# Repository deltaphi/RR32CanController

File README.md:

# RR32CanSwitchboard
Sketch for a Switchboard talking the Maerklin CAN protocol based on the ESP32 NodeMCU-Board.

Special Note: This sketch uses an experimental release of Arduino-ESP32. If you get errors from the compiler or the linker, make sure to (1) clean out as much of PlatformIO as you can without actually uninstalling it and (2) get a fresh checkout of this project.

## CI Status

* Linux Unittest Build

* Embedded Build

* Windows Unittest Build

## Software

This project is built using PlatformIO. It makes use of some features that may
not be easily portable to other Arduino-supported MCUs.

### Library Notes

This project makes use of several libraries. Versioned links to those libraries
are available as git submodules. Note that for seom libraries, using forks from
the same source as this project may be required.

Note that the CAN driver from the lib directory *must not* be present when you
want to compile using the ESP32-IDF driver. Otherwise, the Controller will just
attempt to sit there without sending queued messages or receiving any messages
transmitted on the bus.

### WiFi

This sketch only supports runtime-selection of CAN connection vs. WiFi
connection. The WiFi connection information (SSID, Password, IP of CAN-Gateway)
must be hardcoded.

To support hardcoding, a template file "_wificonfig.h" is provided. Copy the
template to "wificonfig.h" and adjust the configuration information to your
needs.

### Menuing

#### General concept

General: Shift + Direction Change enters the menu (cycles through menus) or leaves the menu without applying any changes.

Menu Levels:

* Level 0/Default: Loco Control
* Level 1: Loco List
* Level 2: Settings Menu

#### Menuing for Accessories

Menuing is required to map turnout input buttons to turnouts or action lists.

TODO: Design.

#### Menuing for Engine Control

Menuing is required for selecting an engine to control. This involves the following usecases:

* Select locally known engine
    * Show list of locally known Engines
    * Select engine
    * Selected Engine is now the active engine

* Select locally unknown engine
    * Verify that at least one local slot for an engine is open
    * If not:
        * Promt the user to remove an engine from the local database to be able to download a new one.
        * Show list of locally known Engines
        * Select an engine.
        * Selected Engine is marked for replacement
    * If yes:
        * Empty engine slot with lowest index is marked for replacement
    * Download list of Engines & total number of known engines from the master controller.
    * Either: Select engine from the master list
        * Details of Selected engine are downloaded.
    * Either: Scroll up/down beyond the currently known set of engine names.
        * If the engine name is unknown, download list of engines from the master controller.
    * Once the download is complete, the selected engine is now the active engine

#### Encoder Acceleration for Engine Control

Formula for acceleration curve: y = m*x + c. x is the time since the last rotation in the same direction,
y is the number of actual increments to apply.

The acceleration is linear. It should be set up so that there is a cutoff at 500ms (no acceleration when
increments are more than half a second apart) and that an "immediate" half rotation (e.g., within 50ms)
hits the opposite end of engine velocity.

Thus, boundary conditions for an encoder with 24 increments per rotaton are:
1 Tick = m*500ms + c
kMaxEngineVelocity Ticks / 12 increments = m * (50ms / 12 increments) + c

Formulas for calculating m and c:

m = (y1 - y2)/(x1 - x2) = (1 - (kMaxEngineVelocity/12))/(500 - (50/12)) = -0.16

c = y1 - m*x1 = 84.03

#### Settings Menu

Menu Entries:

* Turnout mapping
* Action list mapping
* Default connection settings
* WiFi settings

##### Turnout Mapping

When in the Turnout mapping menu:

* Press a button (red or green) for a turnout
* Display shows number of button and whether red or green was pressed (line 1)
* Display shows human-readable number of currently mapped turnout
* Use encoder to adjust the number of the turnout
* pressing the encoder stores the turnout mapping (visual feedback possible?)
* pressing another turnout button switches to settings for that button
* pressing shift + encoder leaves the menu.

Possible extension: Use the function buttons to increase/decrease in steps of 10

### Unit Testing

This project includes a CMake project.
The CMake project is purely used to run unit tests for some parts of the code on your development machine.
You do not need to deal with unit tests (or the CMake project) unless you want to actively develop the software.
To use the CMake project, create an out-of-tree build directoy (in-tree build will confuse the Automagic of PlatformIO).
Unit testing should be possible using any C++14 capable compiler on any Desktop Operating System.
It has been tested successefully using MSVC 2017 Community Edition.

## Hardware

### PCB

There is a KiCAD PCB design included for turning this project into a handheld device.
The PCB is designed for the [Strapubox 2090 case](https://www.reichelt.de/kunststoffgehaeuse-129-x-40-x-26-mm-sp-2090-sw-p33828.html?&trstct=pos_0).

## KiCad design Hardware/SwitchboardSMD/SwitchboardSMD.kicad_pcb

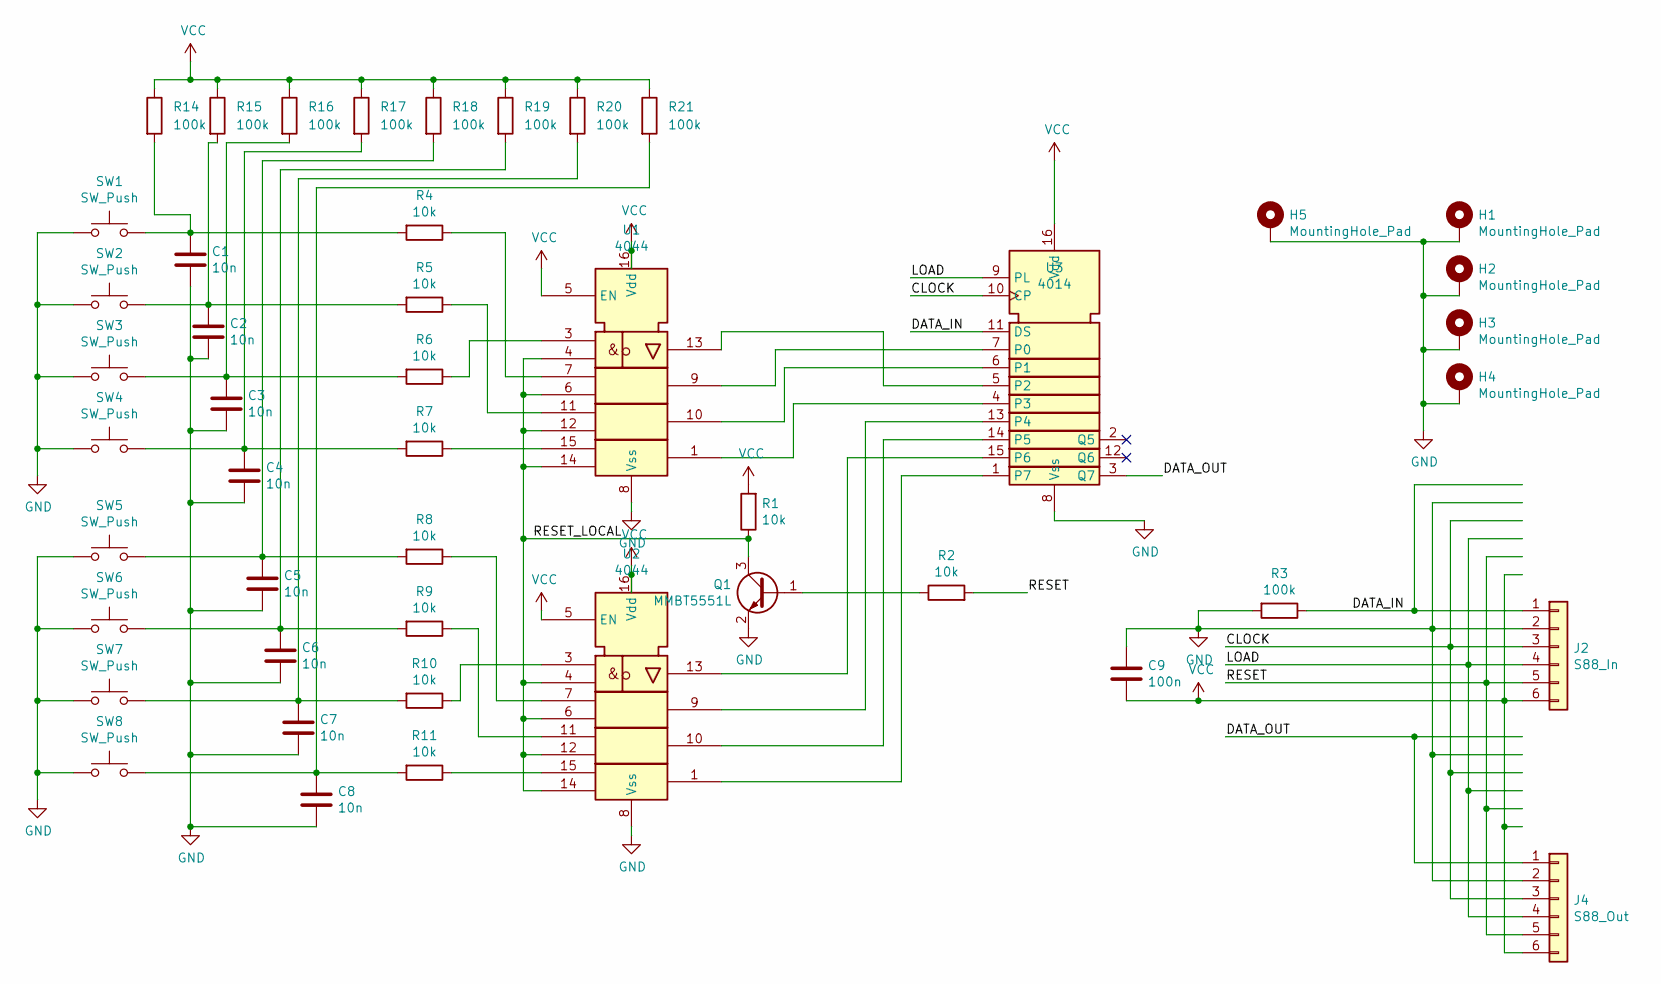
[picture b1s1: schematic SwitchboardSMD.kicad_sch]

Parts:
C1, C2, C3, C4, C5, C6, C7, C8: 10n; C_1206_3216Metric
C9: 100n; C_1206_3216Metric
H1, H2, H3, H4: MountingHole_Pad; MountingHole_2.2mm_M2
H5: MountingHole_Pad; MountingHole_3.2mm_M3_Pad_Via
J2: S88_In; PinSocket_1x06_P2.54mm_Horizontal
J4: S88_Out; PinHeader_1x06_P2.54mm_Horizontal
Q1: MMBT5551L; SOT-23
R1, R2, R4, R5, R6, R7, R8, R9, R10, R11: 10k; R_1206_3216Metric_Pad1.30x1.75mm_HandSolder
R3, R14, R15, R16, R17, R18, R19, R20, R21: 100k; R_1206_3216Metric_Pad1.30x1.75mm_HandSolder
SW1, SW2, SW3, SW4, SW5, SW6, SW7, SW8: SW_Push; SW_PUSH_6mm
U1, U2: 4044; TSSOP-16_4.4x5mm_P0.65mm
U3: 4014; TSSOP-16_4.4x5mm_P0.65mm

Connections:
/CLOCK: J2.3, J4.3, U3.10 (CP)
/DATA_IN: J2.1, R3.1, U3.11 (DS)
/DATA_OUT: J4.1, U3.3 (Q7)
/LOAD: J2.4, J4.4, U3.9 (PL)
/RESET: J2.5, J4.5, R2.2
/RESET_LOCAL: Q1.3 (C), R1.1, U1.4, U1.6, U1.12, U1.14, U2.4, U2.6, U2.12, U2.14
GND: C1.2, C2.2, C3.2, C4.2, C5.2, C6.2, C7.2, C8.2, C9.1, H1.1, H2.1, H3.1, H4.1, H5.1, J2.2, J4.2, Q1.2 (E), R3.2, SW1.1, SW2.1, SW3.1, SW4.1, SW5.1, SW6.1, SW7.1, SW8.1, U1.8 (Vss), U2.8 (Vss), U3.8 (Vss)
unnamed: C1.1, R4.2, R14.2, SW1.2
unnamed: C2.1, R5.2, R15.2, SW2.2
unnamed: C3.1, R6.2, R16.2, SW3.2
unnamed: C4.1, R7.2, R17.2, SW4.2
unnamed: C5.1, R8.2, R18.2, SW5.2
unnamed: C6.1, R9.2, R19.2, SW6.2
unnamed: C7.1, R10.2, R20.2, SW7.2
unnamed: C8.1, R11.2, R21.2, SW8.2
unnamed: Q1.1 (B), R2.1
unnamed: R4.1, U1.7
unnamed: R5.1, U1.11
unnamed: R6.1, U1.3
unnamed: R7.1, U1.15
unnamed: R8.1, U2.7
unnamed: R9.1, U2.11
unnamed: R10.1, U2.3
unnamed: R11.1, U2.15
unnamed: U1.9, U3.7 (P0)
unnamed: U1.10, U3.6 (P1)
unnamed: U1.13, U3.5 (P2)
unnamed: U1.1, U3.4 (P3)
unnamed: U2.9, U3.13 (P4)
unnamed: U2.10, U3.14 (P5)
unnamed: U2.13, U3.15 (P6)
unnamed: U2.1, U3.1 (P7)
VCC: C9.2, J2.6, J4.6, R1.2, R14.1, R15.1, R16.1, R17.1, R18.1, R19.1, R20.1, R21.1, U1.5 (EN), U1.16 (Vdd), U2.5 (EN), U2.16 (Vdd), U3.16 (Vdd)

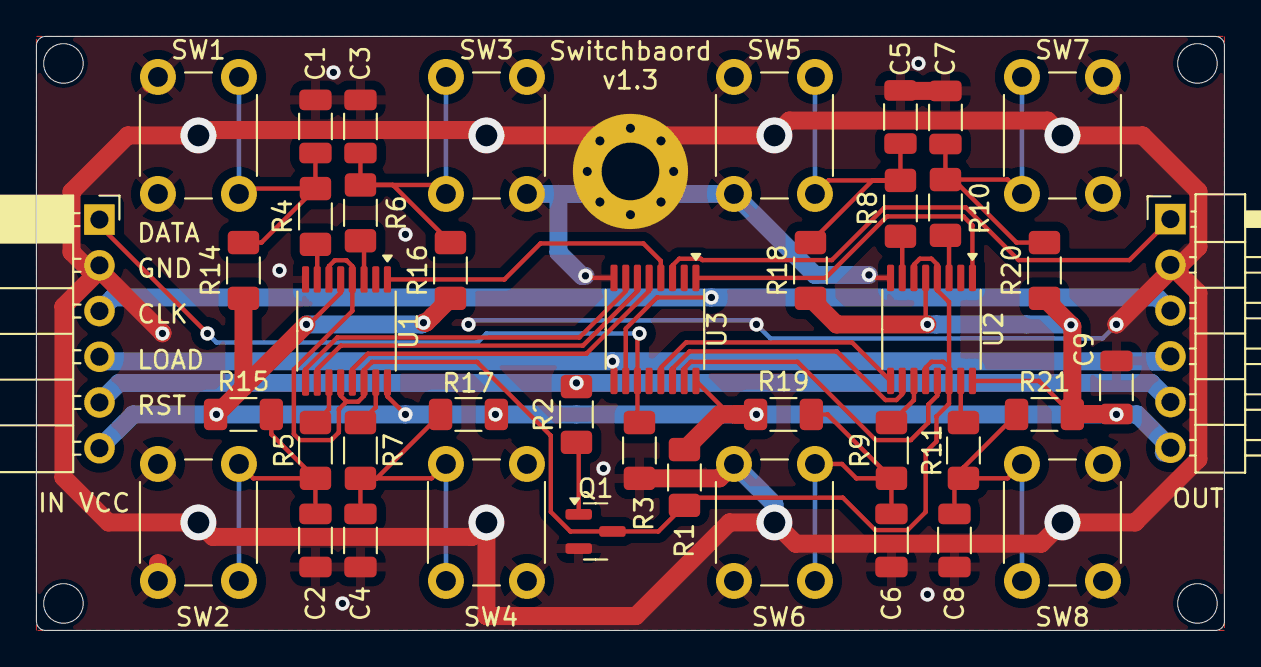
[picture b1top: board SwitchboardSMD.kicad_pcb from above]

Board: 2 copper layers, 66.0 x 33.0 mm, 47 parts (0 on the bottom side), 33 nets.

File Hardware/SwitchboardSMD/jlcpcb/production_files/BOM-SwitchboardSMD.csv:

Comment,Designator,Footprint,LCSC,Quantity
100k,"R14,R15,R16,R17,R18,R19,R20,R21,R3",R_1206_3216Metric_Pad1.30x1.75mm_HandSolder,C17900,9
10k,"R1,R10,R11,R2,R4,R5,R6,R7,R8,R9",R_1206_3216Metric_Pad1.30x1.75mm_HandSolder,C17902,10
10n,"C1,C2,C3,C4,C5,C6,C7,C8",C_1206_3216Metric,C1846,8
100n,C9,C_1206_3216Metric,C24497,1
4014,U3,TSSOP-16_4.4x5mm_P0.65mm,C2877059,1
MMBT5551L,Q1,SOT-23,C41095,1
4044,"U1,U2",TSSOP-16_4.4x5mm_P0.65mm,C74801,2
SW_Push,SW1,SW_PUSH_6mm,,1
MountingHole_Pad,H1,MountingHole_2.2mm_M2,,1
MountingHole_Pad,H2,MountingHole_2.2mm_M2,,1
MountingHole_Pad,H3,MountingHole_2.2mm_M2,,1
MountingHole_Pad,H4,MountingHole_2.2mm_M2,,1
SW_Push,SW2,SW_PUSH_6mm,,1
SW_Push,SW3,SW_PUSH_6mm,,1
SW_Push,SW5,SW_PUSH_6mm,,1
SW_Push,SW6,SW_PUSH_6mm,,1
SW_Push,SW7,SW_PUSH_6mm,,1
SW_Push,SW8,SW_PUSH_6mm,,1
SW_Push,SW4,SW_PUSH_6mm,,1
S88_In,J2,PinSocket_1x06_P2.54mm_Horizontal,,1
S88_Out,J4,PinHeader_1x06_P2.54mm_Horizontal,,1
MountingHole_Pad,H5,MountingHole_3.2mm_M3_Pad_Via,,1

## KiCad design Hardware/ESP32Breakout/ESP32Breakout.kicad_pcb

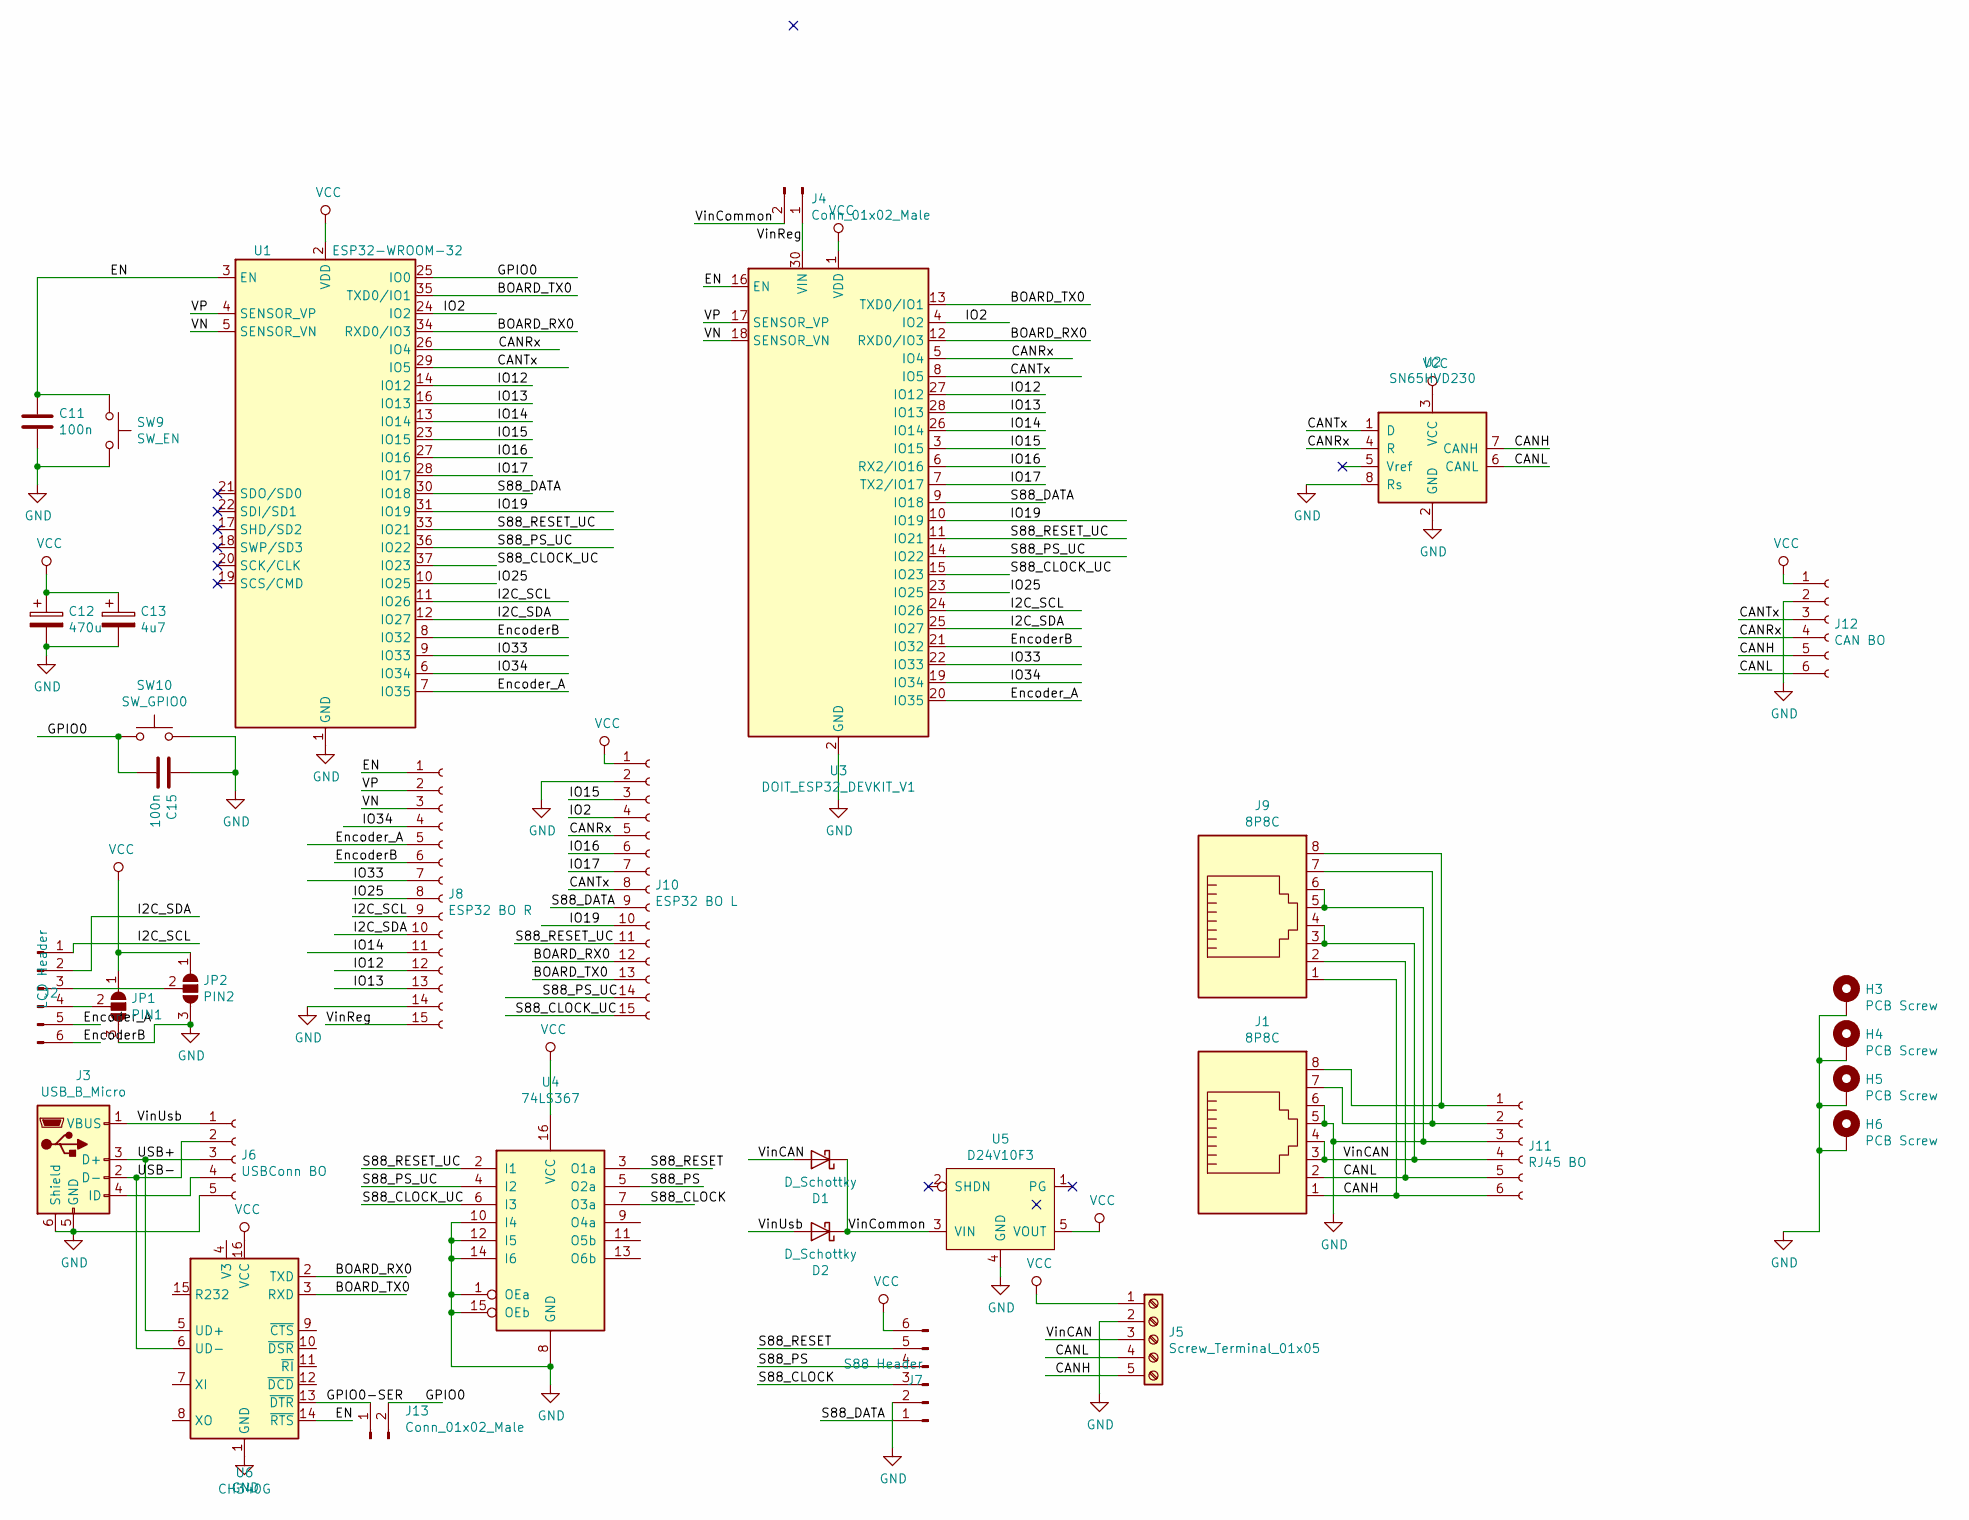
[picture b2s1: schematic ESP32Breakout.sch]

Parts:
C11, C15: 100n; C_Disc_D3.4mm_W2.1mm_P2.50mm
C12: 470u; CP_Radial_D10.0mm_P5.00mm
C13: 4u7; CP_Radial_D5.0mm_P2.50mm
D1, D2: D_Schottky; D_A-405_P7.62mm_Horizontal
H3, H4, H5, H6: PCB Screw; MountingHole_3.2mm_M3_Pad_Via
J1, J9: 8P8C; RJ45_Amphenol_54602-x08_Horizontal
J2: LCD Header; PinHeader_1x06_P2.54mm_Vertical
J3: USB_B_Micro; USB_Micro-B_Molex_47346-0001
J4, J13: Conn_01x02_Male; PinHeader_1x02_P2.54mm_Vertical
J5: Screw_Terminal_01x05; TerminalBlock_4Ucon_1x05_P3.50mm_Vertical
J6: USBConn BO; PinHeader_1x05_P2.54mm_Vertical
J7: S88 Header; PinHeader_1x06_P2.54mm_Vertical
J8: ESP32 BO R; PinHeader_1x15_P2.54mm_Vertical
J10: ESP32 BO L; PinHeader_1x15_P2.54mm_Vertical
J11: RJ45 BO; PinHeader_1x06_P2.54mm_Vertical
J12: CAN BO; PinHeader_1x06_P2.54mm_Vertical
JP1: PIN1; SolderJumper-3_P1.3mm_Open_Pad1.0x1.5mm_NumberLabels
JP2: PIN2; SolderJumper-3_P1.3mm_Open_Pad1.0x1.5mm_NumberLabels
SW9: SW_EN; SW_PUSH_6mm
SW10: SW_GPIO0; SW_PUSH_6mm
U1: ESP32-WROOM-32
U2: SN65HVD230; SOIC-8_3.9x4.9mm_P1.27mm
U3: DOIT_ESP32_DEVKIT_V1; ESP32-DEVKITV1
U4: 74LS367; SOP-16_4.55x10.3mm_P1.27mm
U5: D24V10F3
U6: CH340G; SOIC-16_3.9x9.9mm_P1.27mm

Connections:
/BOARD_RX0: J10.12, U1.34 (RXD0/IO3), U3.12 (RXD0/IO3), U6.2 (TXD)
/BOARD_TX0: J10.13, U1.35 (TXD0/IO1), U3.13 (TXD0/IO1), U6.3 (RXD)
/CANH: J1.1, J5.5, J9.1, J11.6, J12.5, U2.7 (CANH)
/CANL: J1.2, J5.4, J9.2, J11.5, J12.6, U2.6 (CANL)
/CANRx: J10.5, J12.4, U1.26 (IO4), U2.4 (R), U3.5 (IO4)
/CANTx: J10.8, J12.3, U1.29 (IO5), U2.1 (D), U3.8 (IO5)
/EN: C11.1, J8.1, SW9.1, U1.3 (EN), U3.16 (EN), U6.14 (~RTS)
/EncoderB: J2.6, J8.6, U1.8 (IO32), U3.21 (IO32)
/Encoder_A: J2.5, J8.5, U1.7 (IO35), U3.20 (IO35)
/GPIO0: C15.2, J13.2, SW10.1, U1.25 (IO0)
/GPIO0-SER: J13.1, U6.13 (~DTR)
/I2C_SCL: J2.1, J8.9, U1.11 (IO26), U3.24 (IO26)
/I2C_SDA: J2.2, J8.10, U1.12 (IO27), U3.25 (IO27)
/IO2: J10.4, U1.24 (IO2), U3.4 (IO2)
/IO12: J8.12, U1.14 (IO12), U3.27 (IO12)
/IO13: J8.13, U1.16 (IO13), U3.28 (IO13)
/IO14: J8.11, U1.13 (IO14), U3.26 (IO14)
/IO15: J10.3, U1.23 (IO15), U3.3 (IO15)
/IO16: J10.6, U1.27 (IO16), U3.6 (RX2/IO16)
/IO17: J10.7, U1.28 (IO17), U3.7 (TX2/IO17)
/IO19: J10.10, U1.31 (IO19), U3.10 (IO19)
/IO25: J8.8, U1.10 (IO25), U3.23 (IO25)
/IO33: J8.7, U1.9 (IO33), U3.22 (IO33)
/IO34: J8.4, U1.6 (IO34), U3.19 (IO34)
/S88_CLOCK: J7.3, U4.7 (O3a)
/S88_CLOCK_UC: J10.15, U1.37 (IO23), U3.15 (IO23), U4.6 (I3)
/S88_DATA: J7.1, J10.9, U1.30 (IO18), U3.9 (IO18)
/S88_PS: J7.4, U4.5 (O2a)
/S88_PS_UC: J10.14, U1.36 (IO22), U3.14 (IO22), U4.4 (I2)
/S88_RESET: J7.5, U4.3 (O1a)
/S88_RESET_UC: J10.11, U1.33 (IO21), U3.11 (IO21), U4.2 (I1)
/USB+: J3.3 (D+), J6.3, U6.5 (UD+)
/USB-: J3.2 (D-), J6.2, U6.6 (UD-)
/VN: J8.3, U1.5 (SENSOR_VN), U3.18 (SENSOR_VN)
/VP: J8.2, U1.4 (SENSOR_VP), U3.17 (SENSOR_VP)
/VinCAN: D1.2 (A), J1.3, J1.4, J5.3, J9.3, J9.4, J11.4
/VinCommon: D1.1 (K), D2.1 (K), J4.2, U5.3 (VIN)
/VinReg: J4.1, J8.15, U3.30 (VIN)
/VinUsb: D2.2 (A), J3.1 (VBUS), J6.1
GND: C11.2, C12.2, C13.2, C15.1, H3.1, H4.1, H5.1, H6.1, J1.5, J1.6, J3.5 (GND), J3.6 (Shield), J5.2, J6.5, J7.2, J8.14, J9.5, J9.6, J10.2, J11.3, J12.2, JP1.3 (B), JP2.3 (B), SW9.2, SW10.2, U1.1 (GND), U1.15 (GND), U1.38 (GND), U2.2 (GND), U2.8 (Rs), U3.2 (GND), U3.29 (GND), U4.1 (OEa), U4.8 (GND), U4.10 (I4), U4.12 (I5), U4.14 (I6), U4.15 (OEb), U5.4 (GND), U6.1 (GND)
unnamed: J1.7, J9.7, J11.2
unnamed: J1.8, J9.8, J11.1
unnamed: J2.3, JP2.2 (C)
unnamed: J2.4, JP1.2 (C)
unnamed: J3.4 (ID), J6.4
VCC: C12.1, C13.1, J5.1, J7.6, J10.1, J12.1, JP1.1 (A), JP2.1 (A), U1.2 (VDD), U2.3 (VCC), U3.1 (VDD), U4.16 (VCC), U5.5 (VOUT), U6.16 (VCC)

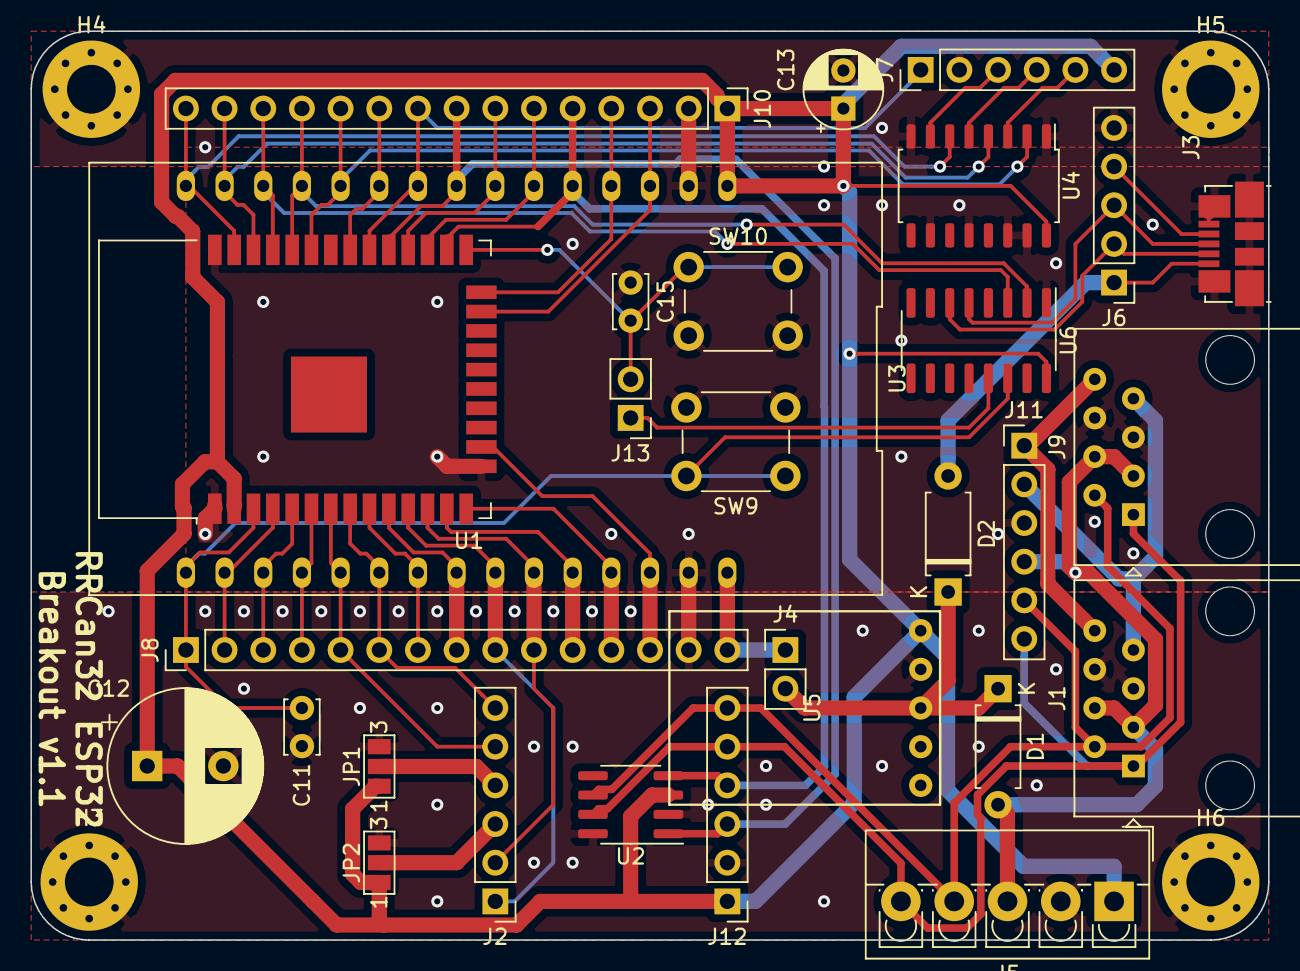
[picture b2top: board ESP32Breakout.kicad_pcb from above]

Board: 2 copper layers, 81.3 x 59.7 mm, 33 parts (0 on the bottom side), 46 nets.

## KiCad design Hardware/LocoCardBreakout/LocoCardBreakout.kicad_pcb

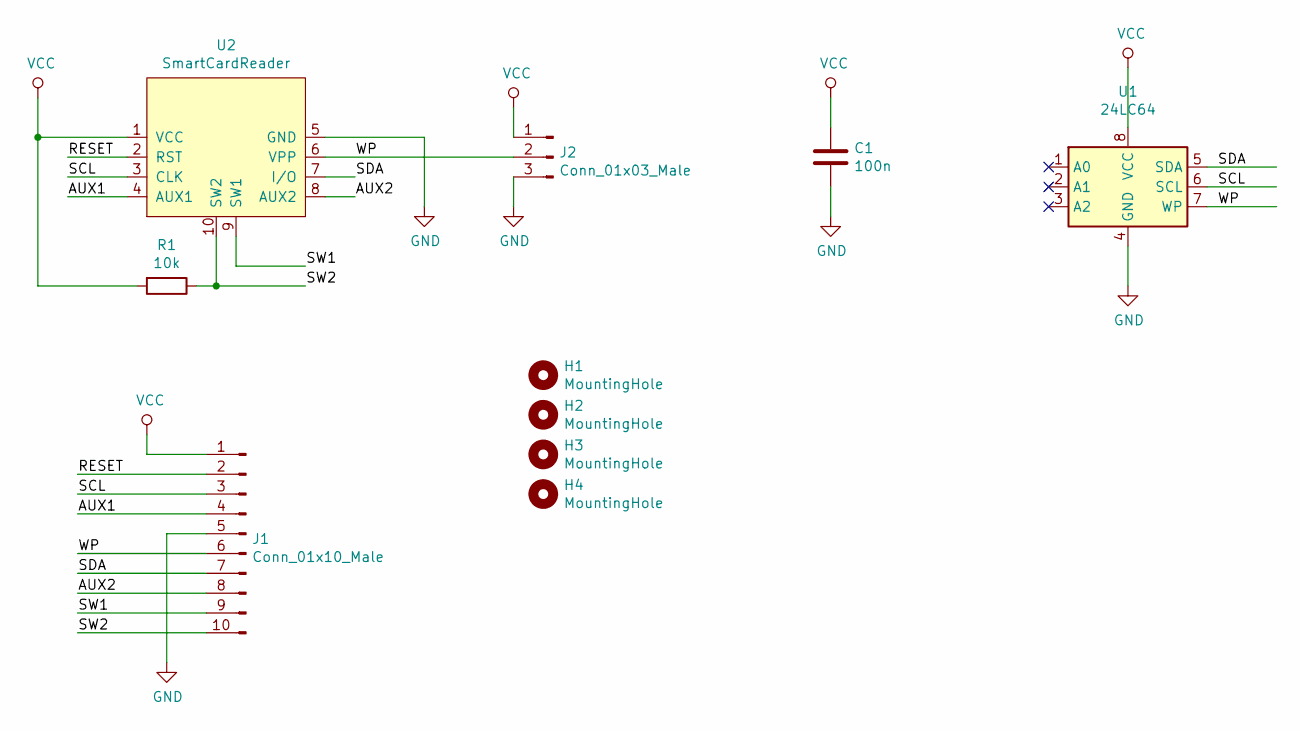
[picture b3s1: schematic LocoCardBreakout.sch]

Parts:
C1: 100n; C_Disc_D3.0mm_W1.6mm_P2.50mm
H1, H2, H3, H4: MountingHole; MountingHole_2.5mm
J1: Conn_01x10_Male; PinHeader_1x10_P2.54mm_Vertical
J2: Conn_01x03_Male; PinHeader_1x03_P2.54mm_Vertical
R1: 10k; R_Axial_DIN0207_L6.3mm_D2.5mm_P7.62mm_Horizontal
U1: 24LC64; DIP-8_W7.62mm_LongPads
U2: SmartCardReader

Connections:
/AUX1: J1.4, U2.4 (AUX1)
/AUX2: J1.8, U2.8 (AUX2)
/RESET: J1.2, U2.2 (RST)
/SCL: J1.3, U1.6 (SCL), U2.3 (CLK)
/SDA: J1.7, U1.5 (SDA), U2.7 (I/O)
/SW1: J1.9, U2.9 (SW1)
/SW2: J1.10, R1.1, U2.10 (SW2)
/WP: J1.6, J2.2, U1.7 (WP), U2.6 (VPP)
GND: C1.2, J1.5, J2.3, U1.4 (GND), U2.5 (GND)
VCC: C1.1, J1.1, J2.1, R1.2, U1.8 (VCC), U2.1 (VCC)

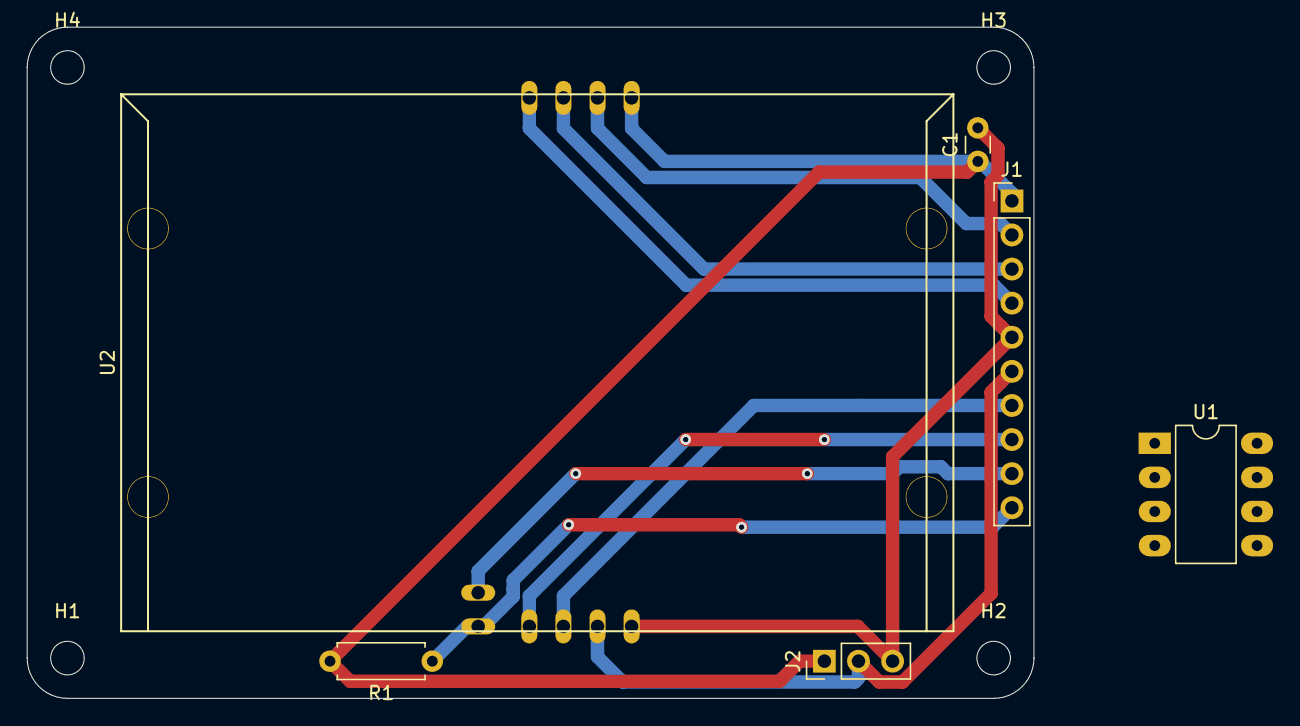
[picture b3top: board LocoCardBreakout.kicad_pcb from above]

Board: 2 copper layers, 75.0 x 50.0 mm, 10 parts (0 on the bottom side), 10 nets.

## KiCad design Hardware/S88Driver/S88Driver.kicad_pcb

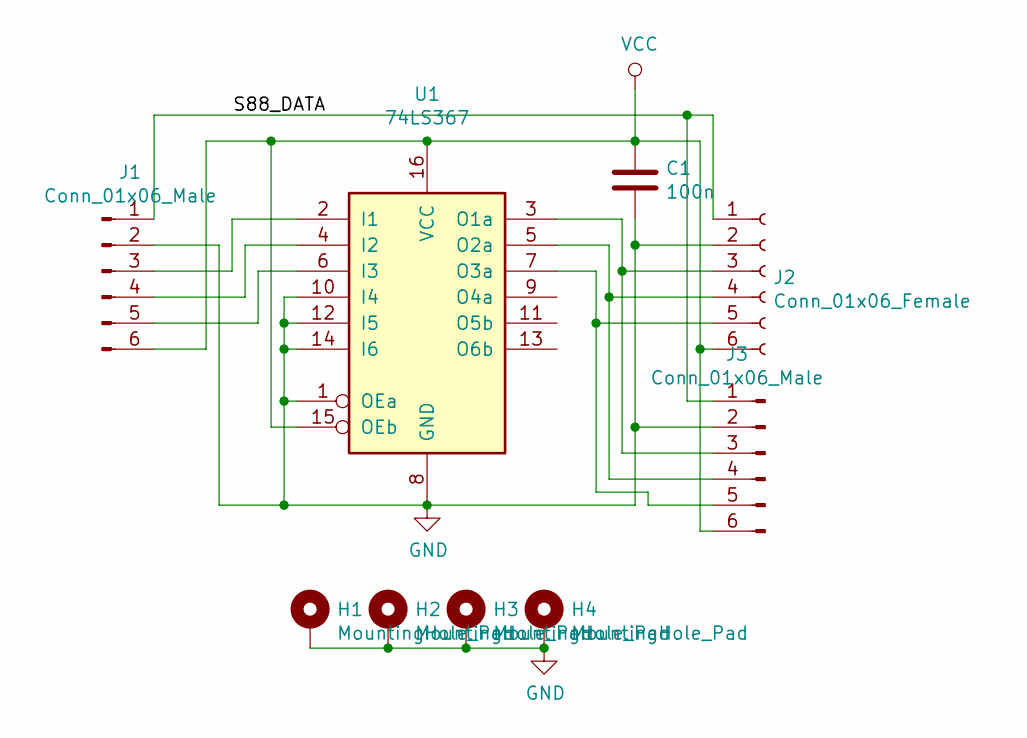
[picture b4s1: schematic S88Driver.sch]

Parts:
C1: 100n; C_Disc_D3.0mm_W1.6mm_P2.50mm
H1, H2, H3, H4: MountingHole_Pad; MountingHole_2.7mm_M2.5_Pad_Via
J1, J3: Conn_01x06_Male; PinSocket_1x06_P2.54mm_Vertical
J2: Conn_01x06_Female; PinSocket_1x06_P2.54mm_Horizontal
U1: 74LS367; DIP-16_W7.62mm_LongPads

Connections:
/S88_DATA: J1.1, J2.1, J3.1
GND: C1.2, H1.1, H2.1, H3.1, H4.1, J1.2, J2.2, J3.2, U1.1 (OEa), U1.8 (GND), U1.10 (I4), U1.12 (I5), U1.14 (I6)
unnamed: J1.3, U1.2 (I1)
unnamed: J1.4, U1.4 (I2)
unnamed: J1.5, U1.6 (I3)
unnamed: J2.3, J3.3, U1.3 (O1a)
unnamed: J2.4, J3.4, U1.5 (O2a)
unnamed: J2.5, J3.5, U1.7 (O3a)
VCC: C1.1, J1.6, J2.6, J3.6, U1.15 (OEb), U1.16 (VCC)

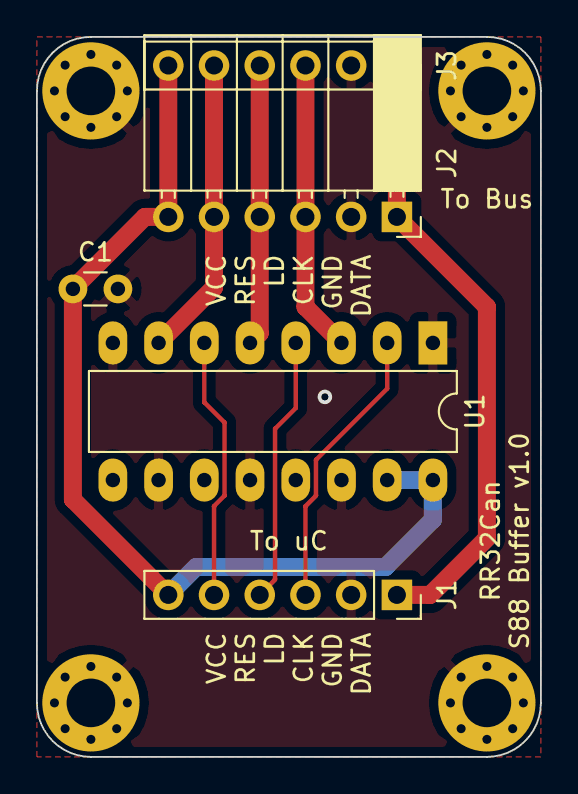
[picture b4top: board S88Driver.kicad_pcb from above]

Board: 2 copper layers, 28.0 x 40.0 mm, 9 parts (0 on the bottom side), 9 nets.

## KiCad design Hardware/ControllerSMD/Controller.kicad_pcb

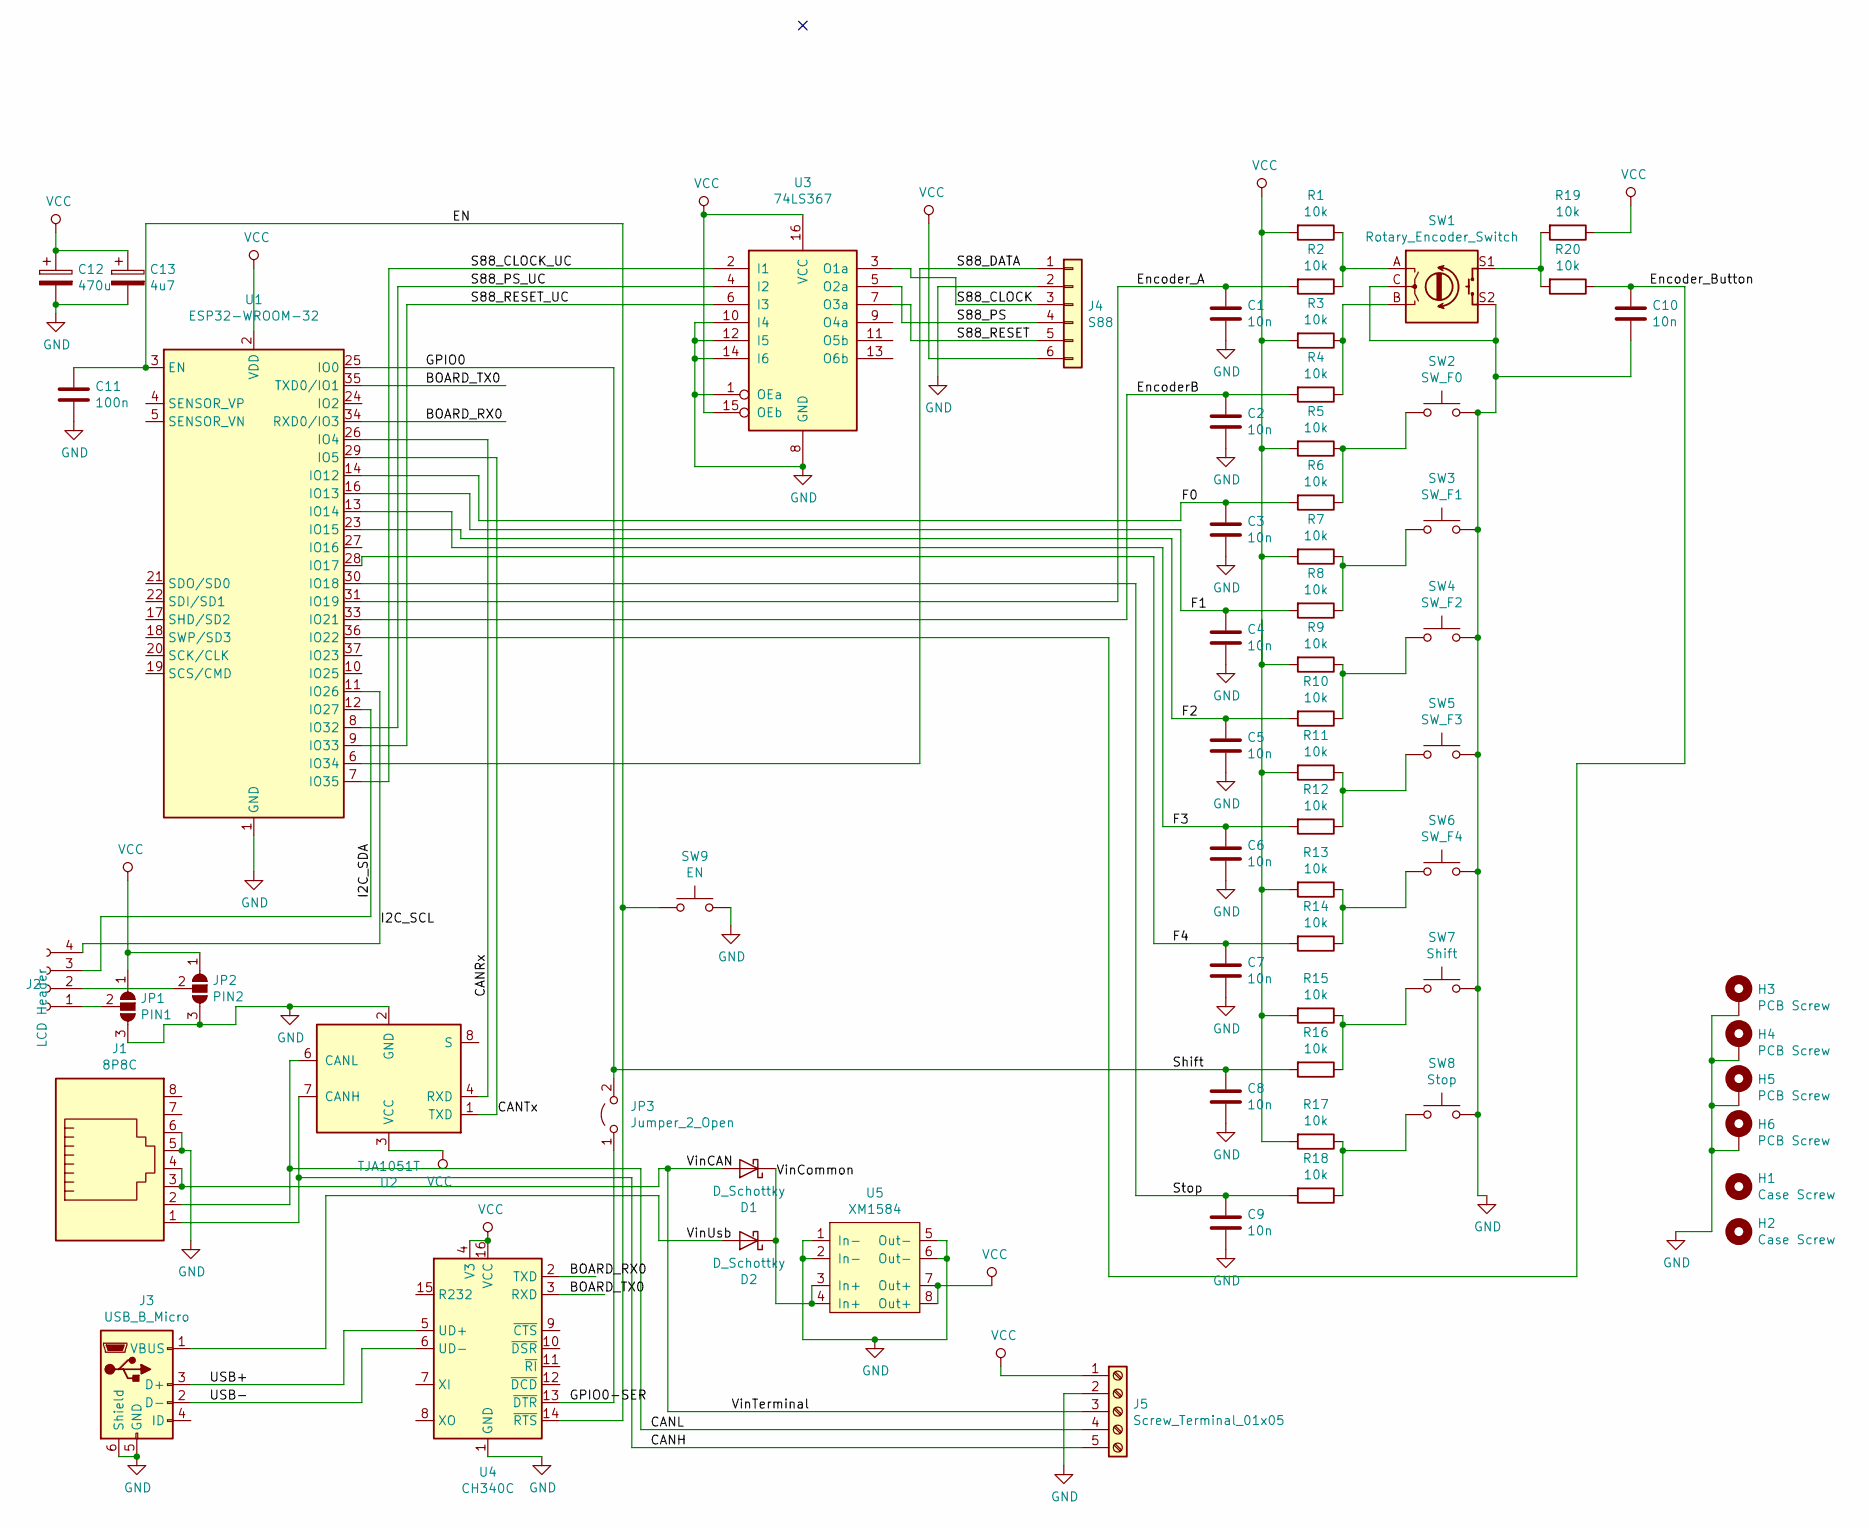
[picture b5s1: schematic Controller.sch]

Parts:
C1, C2, C3, C4, C5, C6, C7, C8, C9, C10: 10n; C_0805_2012Metric_Pad1.15x1.40mm_HandSolder
C11: 100n; C_0805_2012Metric_Pad1.15x1.40mm_HandSolder
C12: 470u; CP_Elec_6.3x7.7
C13: 4u7; CP_EIA-3216-18_Kemet-A_Pad1.58x1.35mm_HandSolder
D1, D2: D_Schottky; D_0603_1608Metric_Pad1.05x0.95mm_HandSolder
H1, H2: Case Screw; MountingHole_5.3mm_M5
H3, H4, H5, H6: PCB Screw; MountingHole_2.7mm_M2.5_Pad_Via
J1: 8P8C; RJ45_Amphenol_54602-x08_Horizontal
J2: LCD Header; PinHeader_1x04_P2.54mm_Vertical
J3: USB_B_Micro; USB_Micro-B_Molex_47346-0001
J4: S88; PinHeader_1x06_P2.54mm_Horizontal
J5: Screw_Terminal_01x05; TerminalBlock_4Ucon_1x05_P3.50mm_Vertical
JP1: PIN1; SolderJumper-3_P1.3mm_Open_Pad1.0x1.5mm_NumberLabels
JP2: PIN2; SolderJumper-3_P1.3mm_Open_Pad1.0x1.5mm_NumberLabels
JP3: Jumper_2_Open; SolderJumper-2_P1.3mm_Open_Pad1.0x1.5mm
R1, R2, R3, R4, R5, R6, R7, R8, R9, R10, R11, R12, R13, R14, R15, R16, R17, R18, R19, R20: 10k; R_0603_1608Metric_Pad1.05x0.95mm_HandSolder
SW1: Rotary_Encoder_Switch; RotaryEncoder_Alps_EC11E-Switch_Vertical_H20mm
SW2: SW_F0; SW_SPST_B3S-1000
SW3: SW_F1; SW_SPST_B3S-1000
SW4: SW_F2; SW_SPST_B3S-1000
SW5: SW_F3; SW_SPST_B3S-1000
SW6: SW_F4; SW_SPST_B3S-1000
SW7: Shift; SW_SPST_B3S-1000
SW8: Stop; SW_SPST_B3S-1000
SW9: EN; SW_Push_1P1T_NO_CK_KMR2
U1: ESP32-WROOM-32
U2: TJA1051T; SOIC-8_3.9x4.9mm_P1.27mm
U3: 74LS367; SOP-16_4.4x10.4mm_P1.27mm
U4: CH340C; SOIC-16_3.9x9.9mm_P1.27mm
U5: XM1584

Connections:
/BOARD_RX0: U1.34 (RXD0/IO3), U4.2 (TXD)
/BOARD_TX0: U1.35 (TXD0/IO1), U4.3 (RXD)
/CANH: J1.1, J5.5, U2.7 (CANH)
/CANL: J1.2, J5.4, U2.6 (CANL)
/CANRx: U1.26 (IO4), U2.4 (RXD)
/CANTx: U1.29 (IO5), U2.1 (TXD)
/EN: C11.1, SW9.1, U1.3 (EN), U4.14 (~RTS)
/EncoderB: C2.2, R4.2, U1.33 (IO21)
/Encoder_A: C1.2, R2.2, U1.31 (IO19)
/Encoder_Button: C10.2, R20.1, U1.36 (IO22)
/F0: C3.2, R6.2, U1.14 (IO12)
/F1: C4.2, R8.2, U1.16 (IO13)
/F2: C5.2, R10.2, U1.23 (IO15)
/F3: C6.2, R12.2, U1.13 (IO14)
/F4: C7.2, R14.2, U1.28 (IO17)
/GPIO0: C8.2, JP3.2 (B), R16.2, U1.25 (IO0)
/GPIO0-SER: JP3.1 (A), U4.13 (~DTR)
/I2C_SCL: J2.4, U1.11 (IO26)
/I2C_SDA: J2.3, U1.12 (IO27)
/S88_CLOCK: J4.3, U3.3 (O1a)
/S88_CLOCK_UC: U1.7 (IO35), U3.2 (I1)
/S88_DATA: J4.1, U1.6 (IO34)
/S88_PS: J4.4, U3.5 (O2a)
/S88_PS_UC: U1.8 (IO32), U3.4 (I2)
/S88_RESET: J4.5, U3.7 (O3a)
/S88_RESET_UC: U1.9 (IO33), U3.6 (I3)
/Stop: C9.2, R18.2, U1.30 (IO18)
/USB+: J3.3 (D+), U4.5 (UD+)
/USB-: J3.2 (D-), U4.6 (UD-)
/VinCAN: D1.2 (A), J1.3, J1.4, J5.3
/VinCommon: D1.1 (K), D2.1 (K), U5.3 (In+), U5.4 (In+)
/VinUsb: D2.2 (A), J3.1 (VBUS)
GND: C1.1, C2.1, C3.1, C4.1, C5.1, C6.1, C7.1, C8.1, C9.1, C10.1, C11.2, C12.2, C13.2, H3.1, H4.1, H5.1, H6.1, J1.5, J1.6, J3.5 (GND), J3.6 (Shield), J4.2, J5.2, JP1.3 (B), JP2.3 (B), SW1.C, SW1.S2, SW2.2, SW3.2, SW4.2, SW5.2, SW6.2, SW7.2, SW8.2, SW9.2, U1.1 (GND), U1.15 (GND), U1.38 (GND), U2.2 (GND), U3.1 (OEa), U3.8 (GND), U3.10 (I4), U3.12 (I5), U3.14 (I6), U4.1 (GND), U5.1 (In-), U5.2 (In-), U5.5 (Out-), U5.6 (Out-)
unnamed: J2.1, JP1.2 (C)
unnamed: J2.2, JP2.2 (C)
unnamed: R1.1, R2.1, SW1.A
unnamed: R3.1, R4.1, SW1.B
unnamed: R5.1, R6.1, SW2.1
unnamed: R7.1, R8.1, SW3.1
unnamed: R9.1, R10.1, SW4.1
unnamed: R11.1, R12.1, SW5.1
unnamed: R13.1, R14.1, SW6.1
unnamed: R15.1, R16.1, SW7.1
unnamed: R17.1, R18.1, SW8.1
unnamed: R19.2, R20.2, SW1.S1
VCC: C12.1, C13.1, J4.6, J5.1, JP1.1 (A), JP2.1 (A), R1.2, R3.2, R5.2, R7.2, R9.2, R11.2, R13.2, R15.2, R17.2, R19.1, U1.2 (VDD), U2.3 (VCC), U3.15 (OEb), U3.16 (VCC), U4.4 (V3), U4.16 (VCC), U5.7 (Out+), U5.8 (Out+)

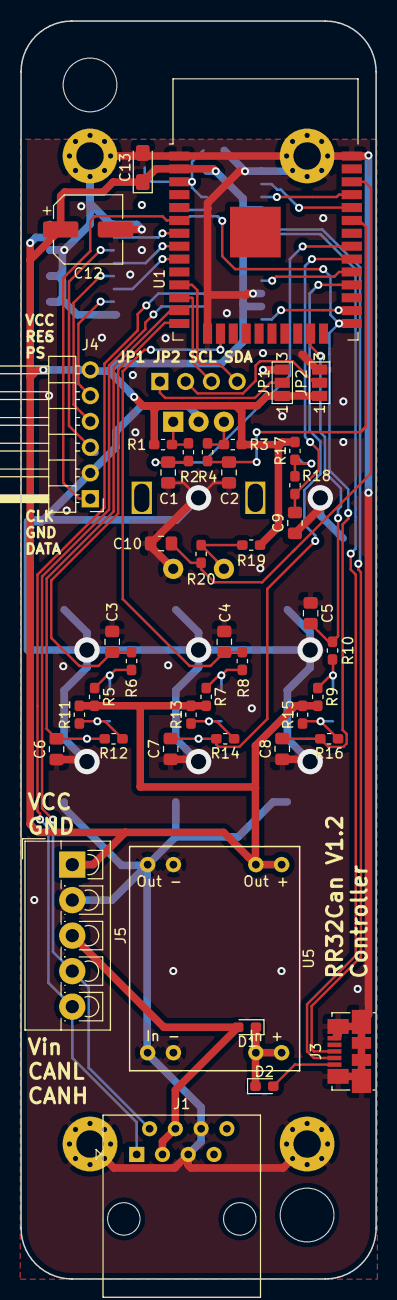
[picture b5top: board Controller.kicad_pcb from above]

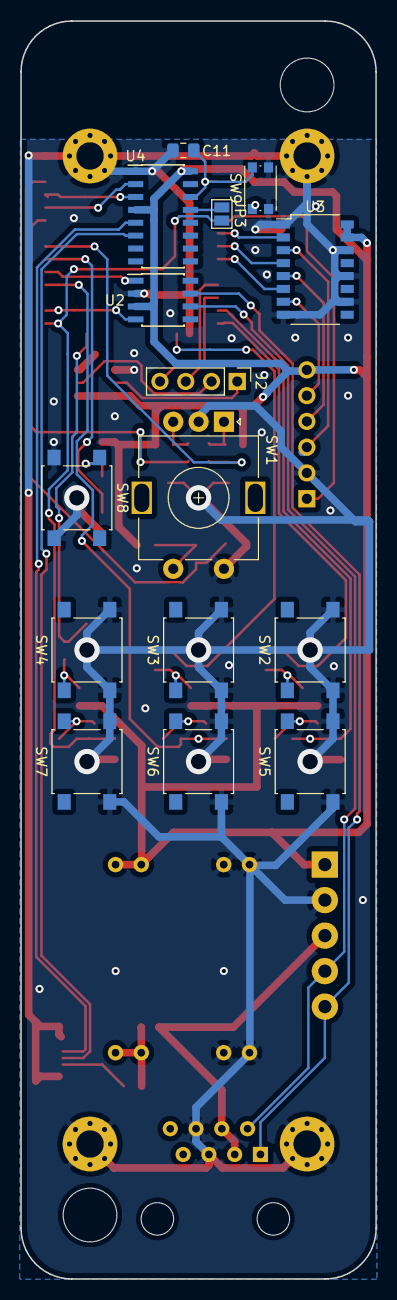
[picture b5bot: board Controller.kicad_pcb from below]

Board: 2 copper layers, 35.0 x 124.0 mm, 63 parts (15 on the bottom side), 46 nets.
